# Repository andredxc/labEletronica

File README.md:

# Laboratório de Eletrônica
PCB design for a simple DC power supply

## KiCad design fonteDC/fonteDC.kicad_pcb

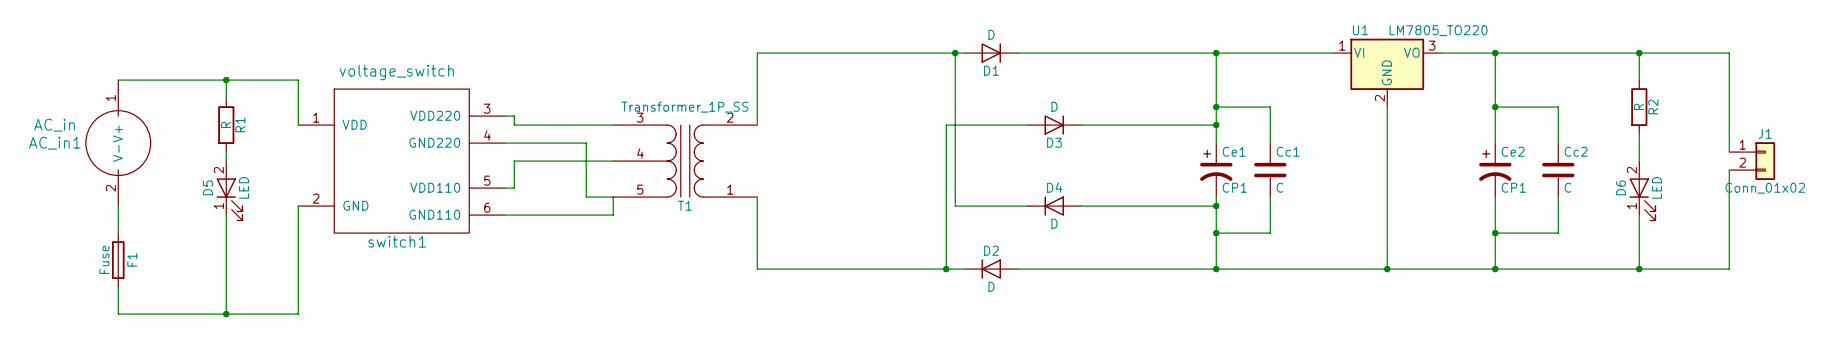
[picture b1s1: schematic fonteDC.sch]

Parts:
AC_in1: AC_in
Cc1, Cc2: C; C_Disc_D5.0mm_W2.5mm_P5.00mm
Ce1: CP1; CP_elet_7mF
Ce2: CP1; CP_elet_10mF
D1, D2, D3, D4: D; D_5W_P12.70mm_Horizontal
D5, D6: LED; D_T-1_P12.70mm_Horizontal
F1: Fuse; fuseholder
J1: Conn_01x02; AC_in
R1, R2: R; R_Axial_DIN0204_L3.6mm_D1.6mm_P7.62mm_Horizontal
T1: Transformer_1P_SS; transformer
U1: LM7805_TO220; TO-220-3_Vertical
switch1: voltage_switch; swich_110_220

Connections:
unnamed: AC_in1.1 (V+), R1.1, switch1.1 (VDD)
unnamed: AC_in1.2 (V-), F1.1
unnamed: Cc1.1, Ce1.1, D1.1 (K), D3.1 (K), U1.1 (VI)
unnamed: Cc1.2, Cc2.2, Ce1.2, Ce2.2, D2.2 (A), D4.2 (A), D6.1 (K), J1.2, U1.2 (GND)
unnamed: Cc2.1, Ce2.1, J1.1, R2.1, U1.3 (VO)
unnamed: D1.2 (A), D4.1 (K), T1.2 (AB)
unnamed: D2.1 (K), D3.2 (A), T1.1 (AA)
unnamed: D5.1 (K), F1.2, switch1.2 (GND)
unnamed: D5.2 (A), R1.2
unnamed: D6.2 (A), R2.2
unnamed: T1.3 (SA), switch1.3 (VDD220)
unnamed: T1.4 (SC), switch1.5 (VDD110)
unnamed: T1.5 (SB), switch1.4 (GND220), switch1.6 (GND110)

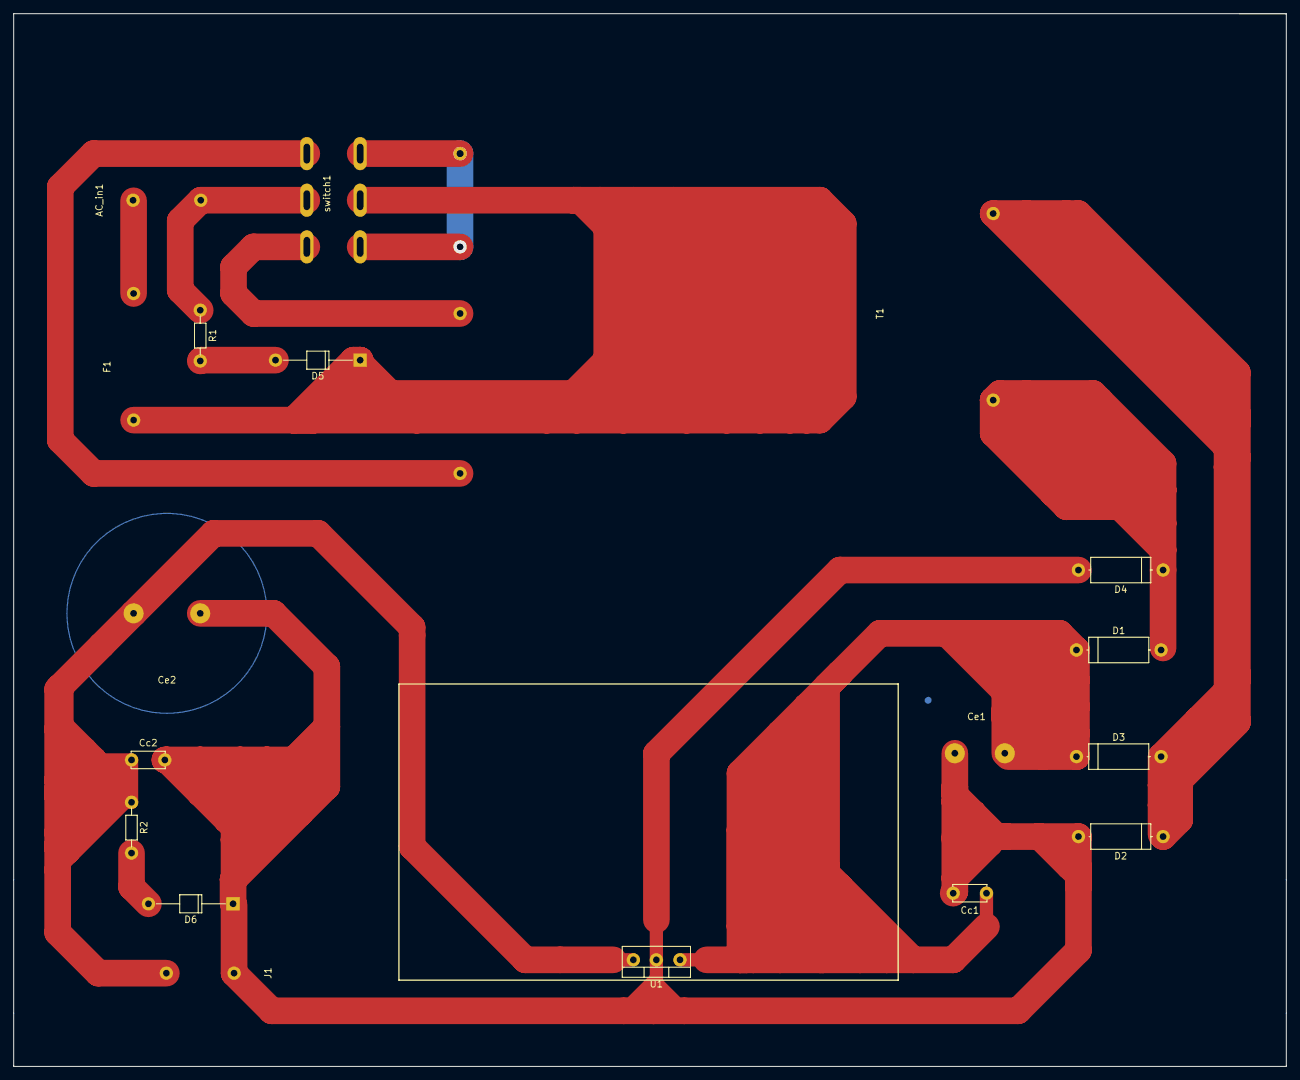
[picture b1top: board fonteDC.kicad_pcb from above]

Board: 2 copper layers, 191.0 x 158.0 mm, 18 parts (0 on the bottom side), 13 nets.

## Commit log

2018-06-15 First version of schematic.
2018-06-15 Finalizando esquemático
2018-06-16 Tudo antes dos footprints dos capacitores e transformador
2018-06-16 Adicionando capacitores e porta fusível
2018-06-16 Adicionando footprints da chave seletora de tensão e do transformador
2018-06-17 almost done.
2018-06-17 Reforçando algumas conexões
2018-06-17 First finished design.
2018-06-18 Finished.
2018-06-24 Organizando o esquemático final
